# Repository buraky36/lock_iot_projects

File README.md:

# lock_iot_projects
Barfas Projects

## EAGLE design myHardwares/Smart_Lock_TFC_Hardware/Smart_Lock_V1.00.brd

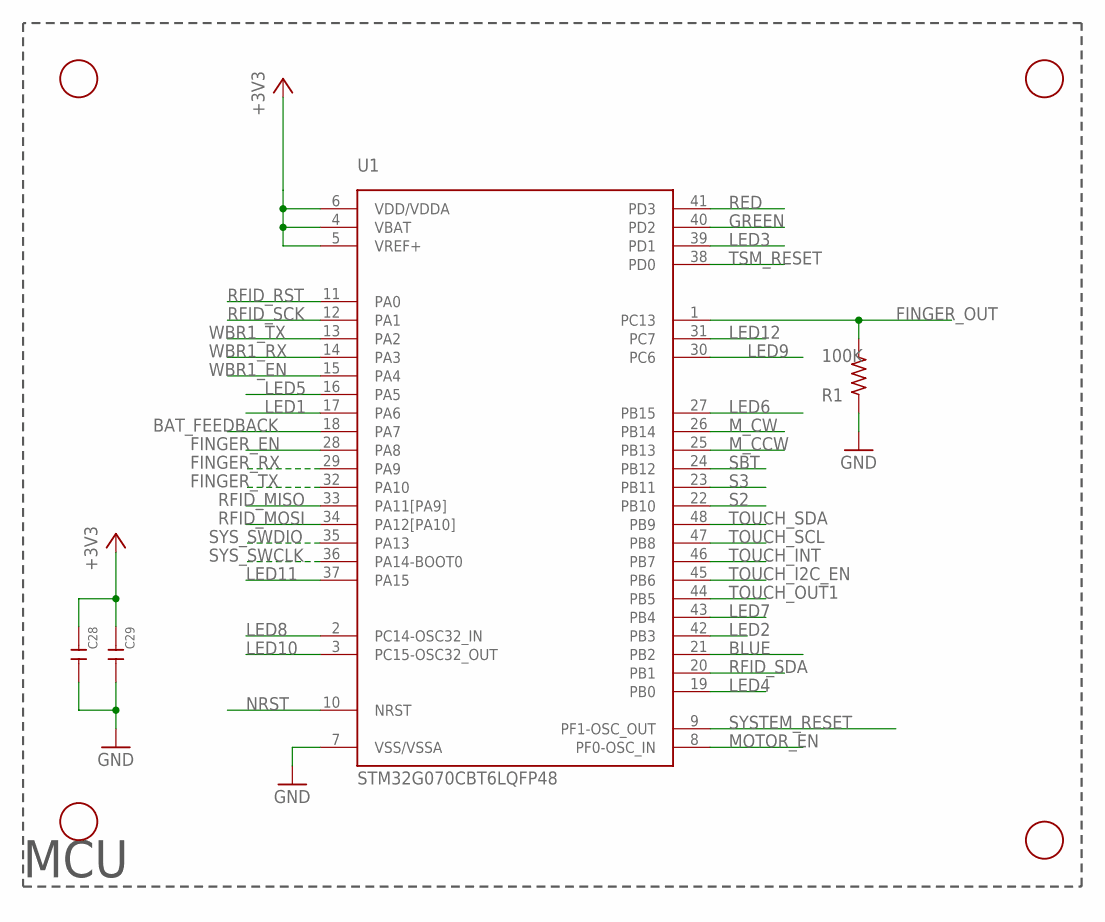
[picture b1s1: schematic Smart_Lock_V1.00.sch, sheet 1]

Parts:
C28, C29: 100nF; C0603
F1, F2, F3, F4: FIDUCIAL; FIDUCIAL_1MM
R1: 100K; R0603
U1: STM32G070CBT6LQFP48; LQFP48

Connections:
+3V3: C28.1, C29.1, U1.4 (VBAT), U1.5 (VREF+), U1.6 (VDD/VDDA); also elsewhere on the board
BAT_FEEDBACK: U1.18 (PA7); also elsewhere on the board
BLUE: U1.21 (PB2); also elsewhere on the board
FINGER_EN: U1.28 (PA8); also elsewhere on the board
FINGER_OUT: R1.1, U1.1 (PC13); also elsewhere on the board
FINGER_RX: U1.29 (PA9); also elsewhere on the board
FINGER_TX: U1.32 (PA10); also elsewhere on the board
GND: C28.2, C29.2, R1.2, U1.7 (VSS/VSSA); also elsewhere on the board
GREEN: U1.40 (PD2); also elsewhere on the board
LED1: U1.17 (PA6); also elsewhere on the board
LED2: U1.42 (PB3); also elsewhere on the board
LED3: U1.39 (PD1); also elsewhere on the board
LED4: U1.19 (PB0); also elsewhere on the board
LED5: U1.16 (PA5); also elsewhere on the board
LED6: U1.27 (PB15); also elsewhere on the board
LED7: U1.43 (PB4); also elsewhere on the board
LED8: U1.2 (PC14-OSC32_IN); also elsewhere on the board
LED9: U1.30 (PC6); also elsewhere on the board
LED10: U1.3 (PC15-OSC32_OUT); also elsewhere on the board
LED11: U1.37 (PA15); also elsewhere on the board
LED12: U1.31 (PC7); also elsewhere on the board
MOTOR_EN: U1.8 (PF0-OSC_IN); also elsewhere on the board
M_CCW: U1.25 (PB13); also elsewhere on the board
M_CW: U1.26 (PB14); also elsewhere on the board
NRST: U1.10 (NRST); also elsewhere on the board
RED: U1.41 (PD3); also elsewhere on the board
RFID_MISO: U1.33 (PA11[PA9]); also elsewhere on the board
RFID_MOSI: U1.34 (PA12[PA10]); also elsewhere on the board
RFID_RST: U1.11 (PA0); also elsewhere on the board
RFID_SCK: U1.12 (PA1); also elsewhere on the board
RFID_SDA: U1.20 (PB1); also elsewhere on the board
S2: U1.22 (PB10); also elsewhere on the board
S3: U1.23 (PB11); also elsewhere on the board
SBT: U1.24 (PB12); also elsewhere on the board
SYSTEM_RESET: U1.9 (PF1-OSC_OUT); also elsewhere on the board
SYS_SWCLK: U1.36 (PA14-BOOT0); also elsewhere on the board
SYS_SWDIO: U1.35 (PA13); also elsewhere on the board
TOUCH_I2C_EN: U1.45 (PB6); also elsewhere on the board
TOUCH_INT: U1.46 (PB7); also elsewhere on the board
TOUCH_OUT1: U1.44 (PB5); also elsewhere on the board
TOUCH_SCL: U1.47 (PB8); also elsewhere on the board
TOUCH_SDA: U1.48 (PB9); also elsewhere on the board
TSM_RESET: U1.38 (PD0); also elsewhere on the board
WBR1_EN: U1.15 (PA4); also elsewhere on the board
WBR1_RX: U1.14 (PA3); also elsewhere on the board
WBR1_TX: U1.13 (PA2); also elsewhere on the board

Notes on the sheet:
MCU

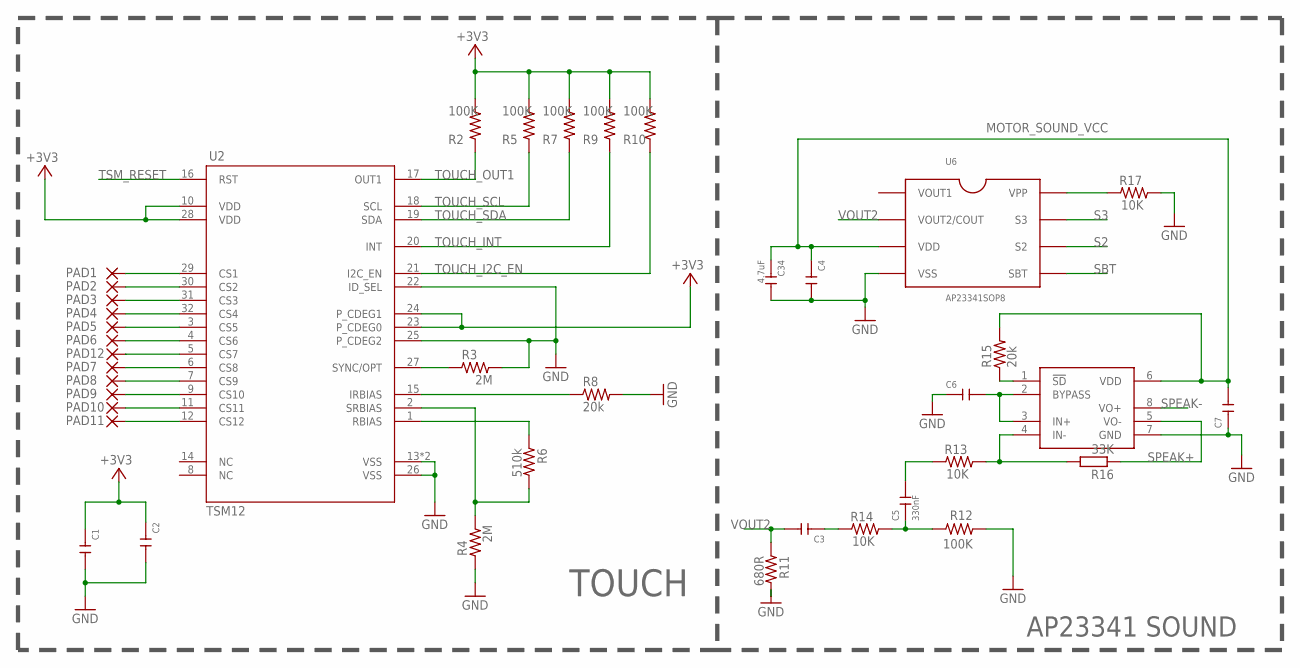
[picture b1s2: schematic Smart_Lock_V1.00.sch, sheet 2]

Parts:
C1, C6, C7: 1uf; C0603
C2, C3, C4: 100nF; C0603
C5: 330nF; C0603
C34: 4.7uF; C0603
PAD1, PAD2, PAD3, PAD4, PAD5, PAD6, PAD7, PAD8, PAD9, PAD10, PAD11, PAD12: WIREPADSMD1,27-254; SMD1,27-2,54
R2, R5, R7, R9, R10, R12: 100K; R0603
R3, R4: 2M; R0603
R6: 510k; R0603
R8, R15: 20k; 0603
R11: 680R; R0603
R13, R14, R17: 10K; R0603
R16: 33K; R0603
U2: TSM12M; QFN_32_UH
U6: AP23341SOP8; SOP8
U7: AP4890; MSOP08

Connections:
+3V3: C1.1, C2.1, R2.1, R5.1, R7.1, R9.1, R10.1, U2.10 (VDD), U2.23 (P_CDEG0), U2.24 (P_CDEG1), U2.28 (VDD); also elsewhere on the board
GND: C1.2, C2.2, C4.2, C6.1, C7.1, C34.2, R3.2, R4.1, R8.2, R11.2, R12.2, R17.2, U2.13 (VSS), U2.22 (ID_SEL), U2.25 (P_CDEG2), U2.26 (VSS), U2.33 (VSS), U6.4 (VSS), U7.7 (GND); also elsewhere on the board
MOTOR_SOUND_VCC: C4.1, C7.2, C34.1, R15.2, U6.3 (VDD), U7.6 (VDD); also elsewhere on the board
unnamed: R17.1, U6.8 (VPP)
unnamed: R15.1, U7.1 (!SD)
unnamed: PAD3.1, U2.31 (CS3)
unnamed: C6.2, U7.2 (BYPASS), U7.3 (IN+)
unnamed: C5.2, R13.1
unnamed: R3.1, U2.27 (SYNC/OPT)
unnamed: R13.2, R16.2, U7.4 (IN-)
unnamed: C3.1, R14.1
unnamed: PAD4.1, U2.32 (CS4)
unnamed: PAD5.1, U2.3 (CS5)
unnamed: PAD6.1, U2.4 (CS6)
unnamed: PAD2.1, U2.30 (CS2)
unnamed: PAD1.1, U2.29 (CS1)
unnamed: PAD7.1, U2.6 (CS8)
unnamed: PAD9.1, U2.9 (CS10)
unnamed: PAD10.1, U2.11 (CS11)
unnamed: R6.1, U2.1 (RBIAS)
unnamed: PAD11.1, U2.12 (CS12)
unnamed: R4.2, R6.2, U2.2 (SRBIAS)
unnamed: PAD12.1, U2.5 (CS7)
unnamed: R8.1, U2.15 (IRBIAS)
unnamed: PAD8.1, U2.7 (CS9)
unnamed: C5.1, R12.1, R14.2
S2: U6.6 (S2); also elsewhere on the board
S3: U6.7 (S3); also elsewhere on the board
SBT: U6.5 (SBT); also elsewhere on the board
SPEAK+: R16.1, U7.5 (VO-); also elsewhere on the board
SPEAK-: U7.8 (VO+); also elsewhere on the board
TOUCH_I2C_EN: R10.2, U2.21 (I2C_EN); also elsewhere on the board
TOUCH_INT: R9.2, U2.20 (INT); also elsewhere on the board
TOUCH_OUT1: R2.2, U2.17 (OUT1); also elsewhere on the board
TOUCH_SCL: R5.2, U2.18 (SCL); also elsewhere on the board
TOUCH_SDA: R7.2, U2.19 (SDA); also elsewhere on the board
TSM_RESET: U2.16 (RST); also elsewhere on the board
VOUT2: C3.2, R11.1, U6.2 (VOUT2/COUT)

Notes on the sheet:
TOUCH
AP23341 SOUND

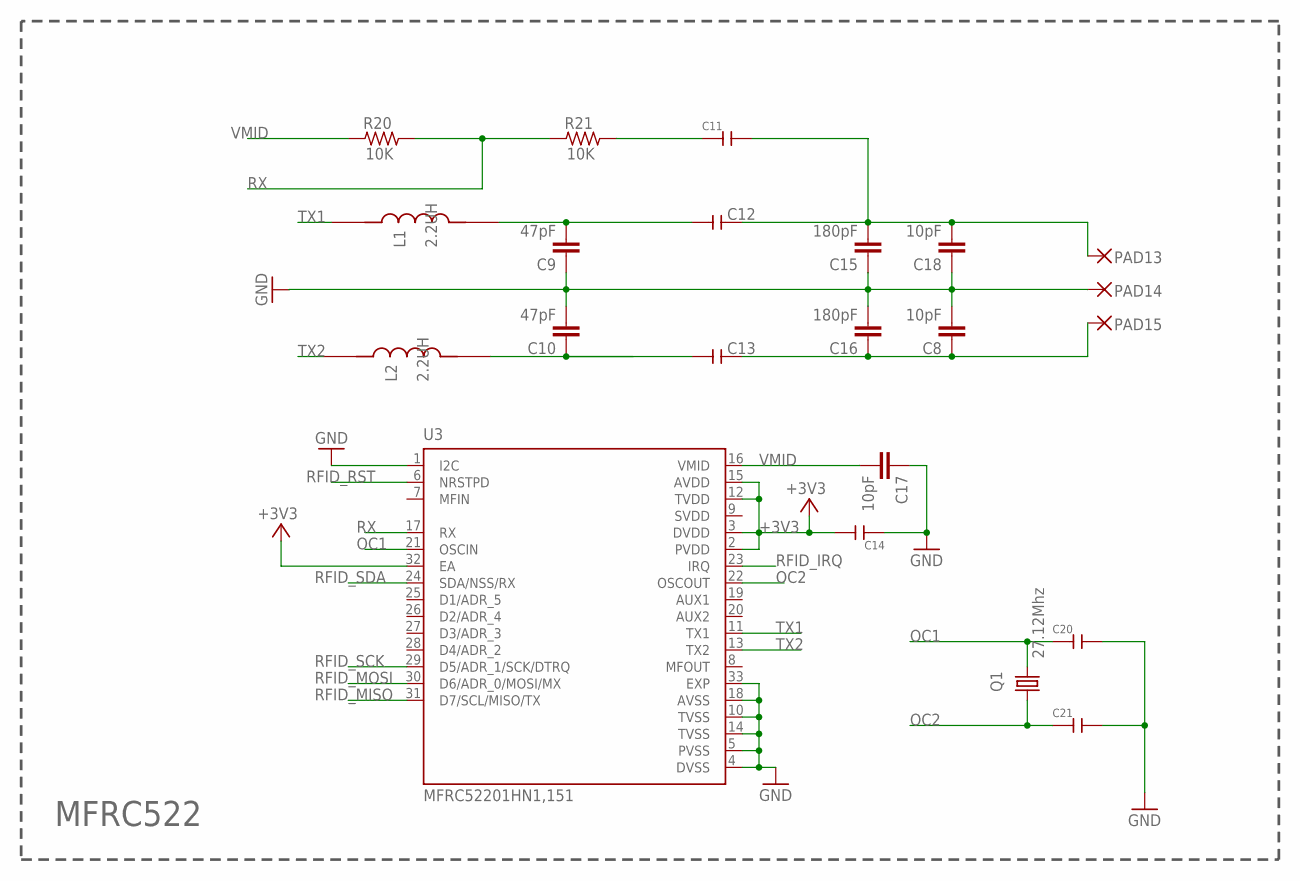
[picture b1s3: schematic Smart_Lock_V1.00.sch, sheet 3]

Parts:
C8, C17, C18: 10pF; C0603
C9, C10: 47pF; C0603
C11, C14: 100nF; C0603
C12, C13, C20, C21: 15pf; C0603
C15, C16: 180pF; C0603
L1, L2: 2.2UH; INDC2012X105N
PAD13, PAD14, PAD15: WIREPADSMD5-1,8; 5-1,8
Q1: 27.12Mhz; 2.5X2.0_KX-6
R20, R21: 10K; R0603
U3: MFRC52201HN1,151; QFN50P500X500X100-33N

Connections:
+3V3: C14.2, U3.2 (PVDD), U3.3 (DVDD), U3.12 (TVDD), U3.15 (AVDD), U3.32 (EA); also elsewhere on the board
ANT: C11.2, C12.2, C15.2, C18.2, PAD13.1
ANT2: C8.1, C13.2, C16.1, PAD15.1
GND: C8.2, C9.1, C10.2, C14.1, C15.1, C16.2, C17.1, C18.1, C20.2, C21.2, PAD14.1, U3.1 (I2C), U3.4 (DVSS), U3.5 (PVSS), U3.10 (TVSS), U3.14 (TVSS), U3.18 (AVSS), U3.33 (EXP); also elsewhere on the board
unnamed: C11.1, R21.2
unnamed: C9.2, C12.1, L1.2
unnamed: C10.1, C13.1, L2.2
OC1: C20.1, Q1.3 (2), U3.21 (OSCIN)
OC2: C21.1, Q1.1, U3.22 (OSCOUT)
RFID_IRQ: U3.23 (IRQ)
RFID_MISO: U3.31 (D7/SCL/MISO/TX); also elsewhere on the board
RFID_MOSI: U3.30 (D6/ADR_0/MOSI/MX); also elsewhere on the board
RFID_RST: U3.6 (NRSTPD); also elsewhere on the board
RFID_SCK: U3.29 (D5/ADR_1/SCK/DTRQ); also elsewhere on the board
RFID_SDA: U3.24 (SDA/NSS/RX); also elsewhere on the board
RX: R20.2, R21.1, U3.17 (RX)
SVDD: U3.9 (SVDD)
TX1: L1.1, U3.11 (TX1)
TX2: L2.1, U3.13 (TX2)
VMID: C17.2, R20.1, U3.16 (VMID)

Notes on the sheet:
MFRC522

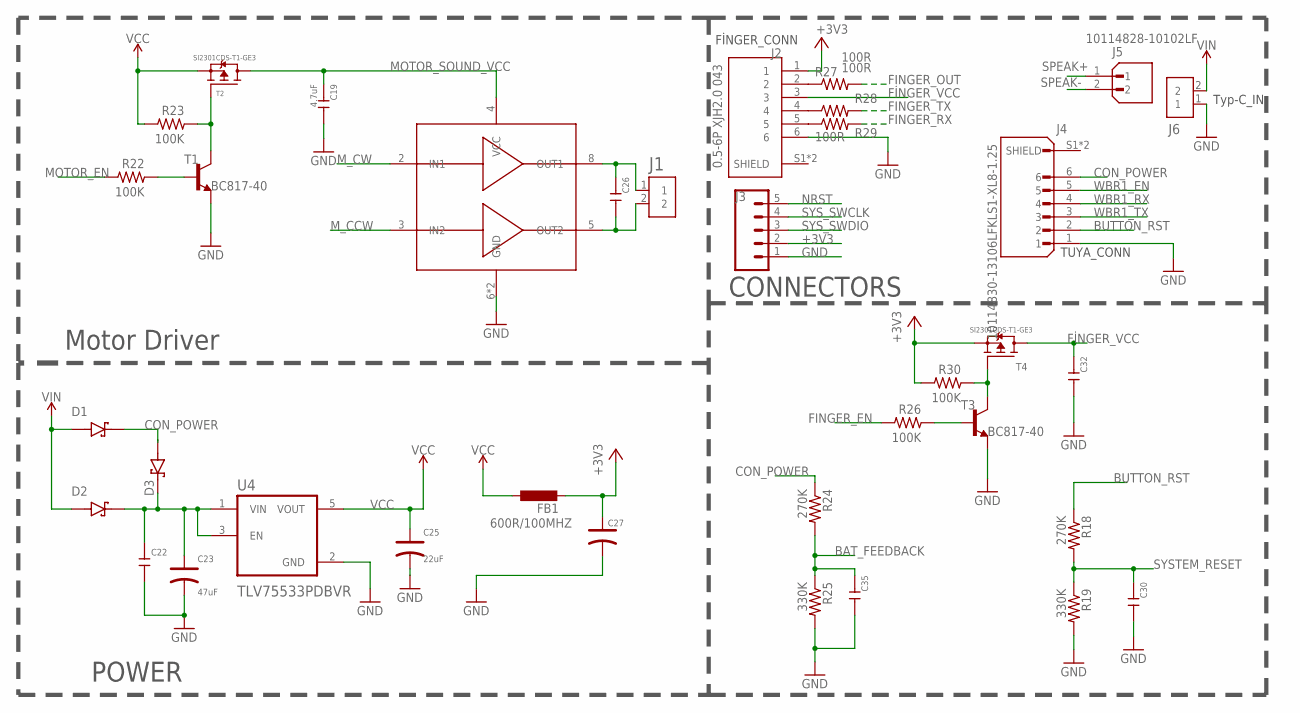
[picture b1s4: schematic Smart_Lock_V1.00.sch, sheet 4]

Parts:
C19: 4.7uF; C0603
C22, C26, C30, C32, C35: 100nF; C0603
C23: 47uF; AVX-B
C25: 22uF; CT1206
C27: 10uf; AVX-B
D1, D2, D3: 1N5819HW-7-F; SOD3715X145N
FB1: 600R/100MHZ; L2012C
J1, J6: B2B-PH-SM4-TB(LF)(SN)
J2: 0.5-6P XJH2.0 043; WE_68710614522
J3: CONN_05; 1X05
J4: 10114830-13106LFKLS1-XL8-1.25; 1X6PIN_1.25MM
J5: 10114828-10102LF; AMPHENOL_10114828-10102LF
R18, R24: 270K; 0603
R19, R25: 330K; 0603
R22, R23, R26, R30: 100K; R0603
R27, R28, R29: 100R; R0402
T1, T3: BC817-40; SOT23-BEC
T2, T4: SI2301CDS-T1-GE3; SOT-23
U4: TLV75533PDBVR; SOT95P285X140-5N
U5: TC118S8; SO08

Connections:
+3V3: C27.+, FB1.2, J2.1, J3.2, R30.1, T4.2 (S); also elsewhere on the board
BAT_FEEDBACK: C35.1, R24.2, R25.1; also elsewhere on the board
BUTTON_RST: J4.2, R18.1
CON_POWER: D1.C (K), D3.A, J4.6, R24.1
FINGER_EN: R26.1; also elsewhere on the board
FINGER_OUT: R27.2; also elsewhere on the board
FINGER_RX: R29.2; also elsewhere on the board
FINGER_TX: R28.2; also elsewhere on the board
FİNGER_VCC: C32.1, J2.3, T4.3 (D)
GND: C19.2, C22.2, C23.-, C25.-, C27.-, C30.2, C32.2, C35.2, J2.6, J3.1, J4.1, J6.1, R19.2, R25.2, T1.E, T3.E, U4.2 (GND), U5.6 (GND), U5.7 (GND); also elsewhere on the board
MOTOR_EN: R22.1; also elsewhere on the board
MOTOR_SOUND_VCC: C19.1, T2.3 (D), U5.4 (VCC); also elsewhere on the board
M_CCW: U5.3 (IN2); also elsewhere on the board
M_CW: U5.2 (IN1); also elsewhere on the board
unnamed: C22.1, C23.+, D2.C (K), D3.C (K), U4.1 (VIN), U4.3 (EN)
unnamed: C26.1, J1.1, U5.8 (OUT1)
unnamed: R26.2, T3.B
unnamed: C26.2, J1.2, U5.5 (OUT2)
unnamed: R30.2, T3.C, T4.1 (G)
unnamed: R22.2, T1.B
unnamed: R23.2, T1.C, T2.1 (G)
unnamed: J2.2, R27.1
unnamed: J2.4, R28.1
unnamed: J2.5, R29.1
NRST: J3.5; also elsewhere on the board
SPEAK+: J5.1; also elsewhere on the board
SPEAK-: J5.2; also elsewhere on the board
SYSTEM_RESET: C30.1, R18.2, R19.1; also elsewhere on the board
SYS_SWCLK: J3.4; also elsewhere on the board
SYS_SWDIO: J3.3; also elsewhere on the board
VCC: C25.+, FB1.1, R23.1, T2.2 (S), U4.5 (VOUT)
VIN: D1.A, D2.A, J6.2
WBR1_EN: J4.5; also elsewhere on the board
WBR1_RX: J4.4; also elsewhere on the board
WBR1_TX: J4.3; also elsewhere on the board

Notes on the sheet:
POWER
CONNECTORS
Motor Driver
Typ-C_IN
TUYA_CONN
FİNGER_CONN

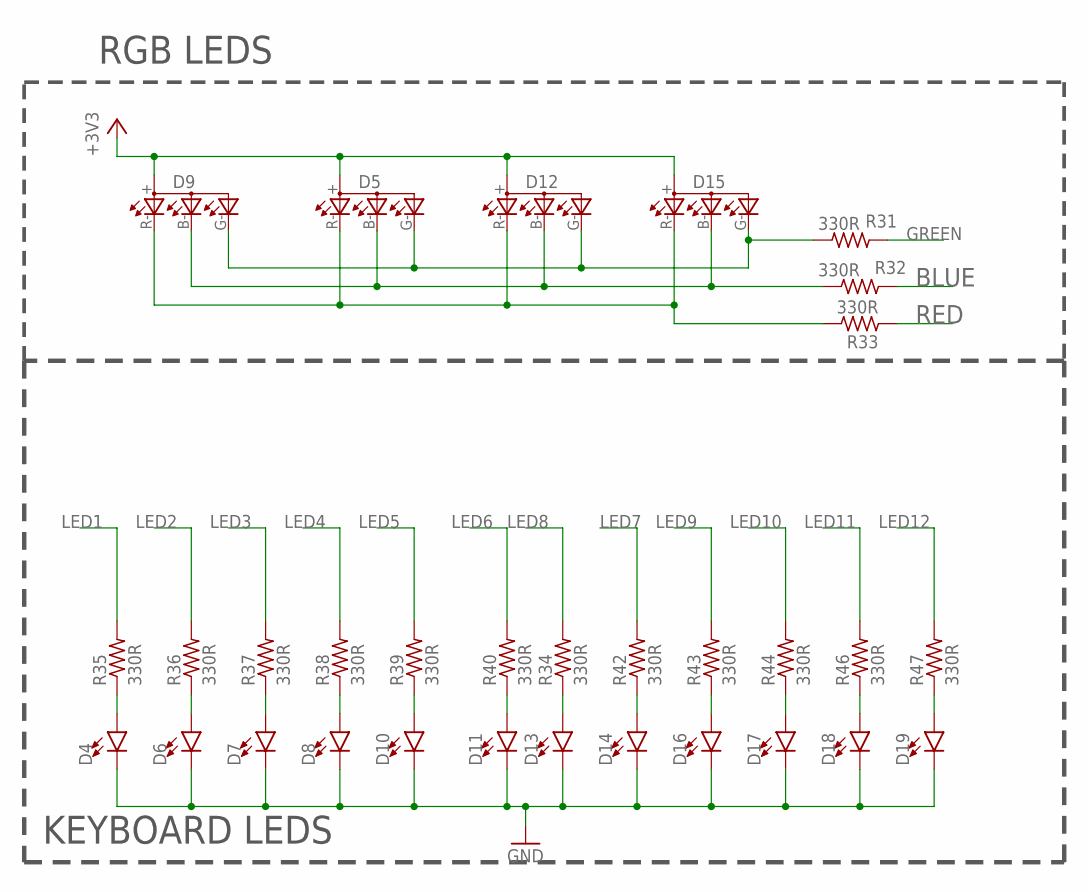
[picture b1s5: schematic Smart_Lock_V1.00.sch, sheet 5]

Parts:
D4, D6, D7, D8, D10, D11, D13, D14, D16, D17, D18, D19: HL-PST-1608H233W-HF4; LED-0603
D5, D9, D12, D15: FM-3510RGBA-SG; SMD-4P,1X3MM
R31, R32, R33: 330R; R0603
R34, R35, R36, R37, R38, R39, R40, R42, R43, R44, R46, R47: 330R; R0402

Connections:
+3V3: D5.+ (A), D9.+ (A), D12.+ (A), D15.+ (A); also elsewhere on the board
BLUE: R32.2; also elsewhere on the board
GND: D4.C, D6.C, D7.C, D8.C, D10.C, D11.C, D13.C, D14.C, D16.C, D17.C, D18.C, D19.C; also elsewhere on the board
GREEN: R31.2; also elsewhere on the board
LED1: R35.2; also elsewhere on the board
LED2: R36.2; also elsewhere on the board
LED3: R37.2; also elsewhere on the board
LED4: R38.2; also elsewhere on the board
LED5: R39.2; also elsewhere on the board
LED6: R40.2; also elsewhere on the board
LED7: R42.2; also elsewhere on the board
LED8: R34.2; also elsewhere on the board
LED9: R43.2; also elsewhere on the board
LED10: R44.2; also elsewhere on the board
LED11: R46.2; also elsewhere on the board
LED12: R47.2; also elsewhere on the board
unnamed: D13.A, R34.1
unnamed: D5.G- (CGREEN), D9.G- (CGREEN), D12.G- (CGREEN), D15.G- (CGREEN), R31.1
unnamed: D5.B- (CBLUE), D9.B- (CBLUE), D12.B- (CBLUE), D15.B- (CBLUE), R32.1
unnamed: D4.A, R35.1
unnamed: D6.A, R36.1
unnamed: D5.R- (CRED), D9.R- (CRED), D12.R- (CRED), D15.R- (CRED), R33.1
unnamed: D7.A, R37.1
unnamed: D8.A, R38.1
unnamed: D10.A, R39.1
unnamed: D11.A, R40.1
unnamed: D14.A, R42.1
unnamed: D16.A, R43.1
unnamed: D17.A, R44.1
unnamed: D18.A, R46.1
unnamed: D19.A, R47.1
RED: R33.2; also elsewhere on the board

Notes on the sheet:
KEYBOARD LEDS
RGB LEDS

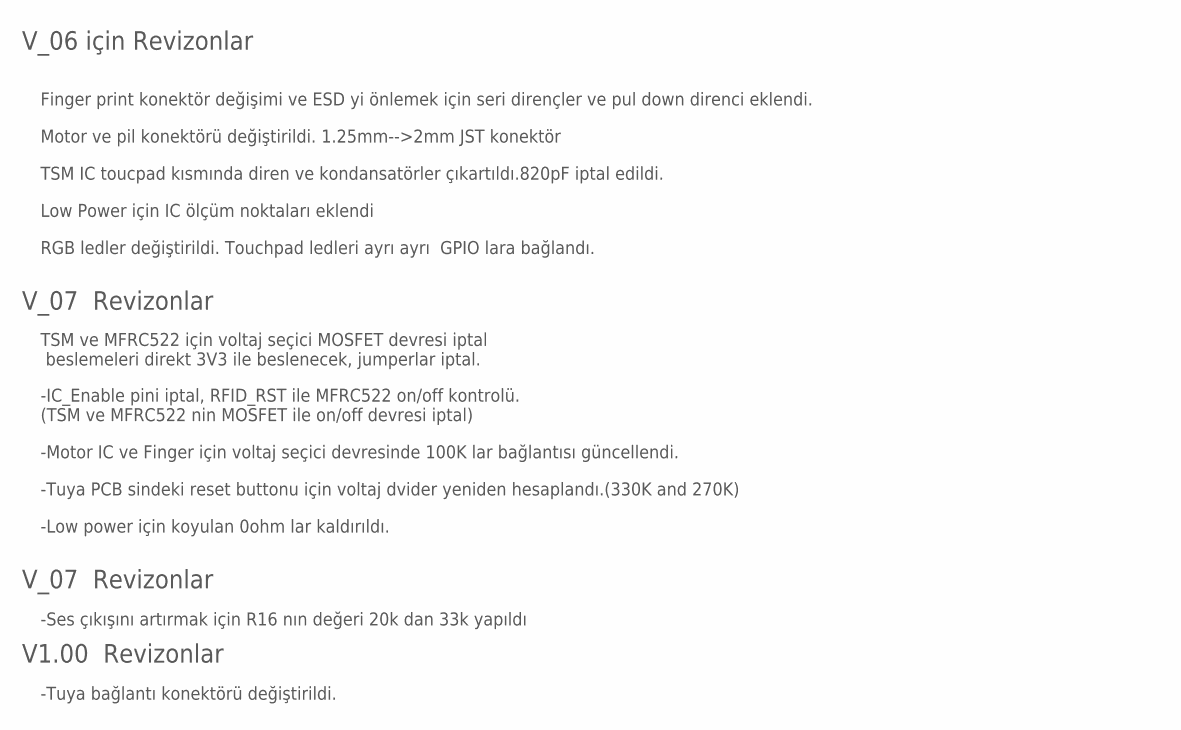
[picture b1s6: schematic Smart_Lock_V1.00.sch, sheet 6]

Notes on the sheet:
Finger print konektör değişimi ve ESD yi önlemek için seri dirençler ve pul down direnci eklendi.
Motor ve pil konektörü değiştirildi. 1.25mm-->2mm JST konektör
TSM IC toucpad kısmında diren ve kondansatörler çıkartıldı.820pF iptal edildi.
Low Power için IC ölçüm noktaları eklendi
RGB ledler değiştirildi. Touchpad ledleri ayrı ayrı GPIO lara bağlandı.
V_06 için Revizonlar
V_07 Revizonlar
TSM ve MFRC522 için voltaj seçici MOSFET devresi iptal beslemeleri direkt 3V3 ile beslenecek, jumperlar iptal.
-IC_Enable pini iptal, RFID_RST ile MFRC522 on/off kontrolü. (TSM ve MFRC522 nin MOSFET ile on/off devresi iptal)
-Motor IC ve Finger için voltaj seçici devresinde 100K lar bağlantısı güncellendi.
-Tuya PCB sindeki reset buttonu için voltaj dvider yeniden hesaplandı.(330K and 270K)
-Low power için koyulan 0ohm lar kaldırıldı.
-Ses çıkışını artırmak için R16 nın değeri 20k dan 33k yapıldı
V1.00 Revizonlar
-Tuya bağlantı konektörü değiştirildi.

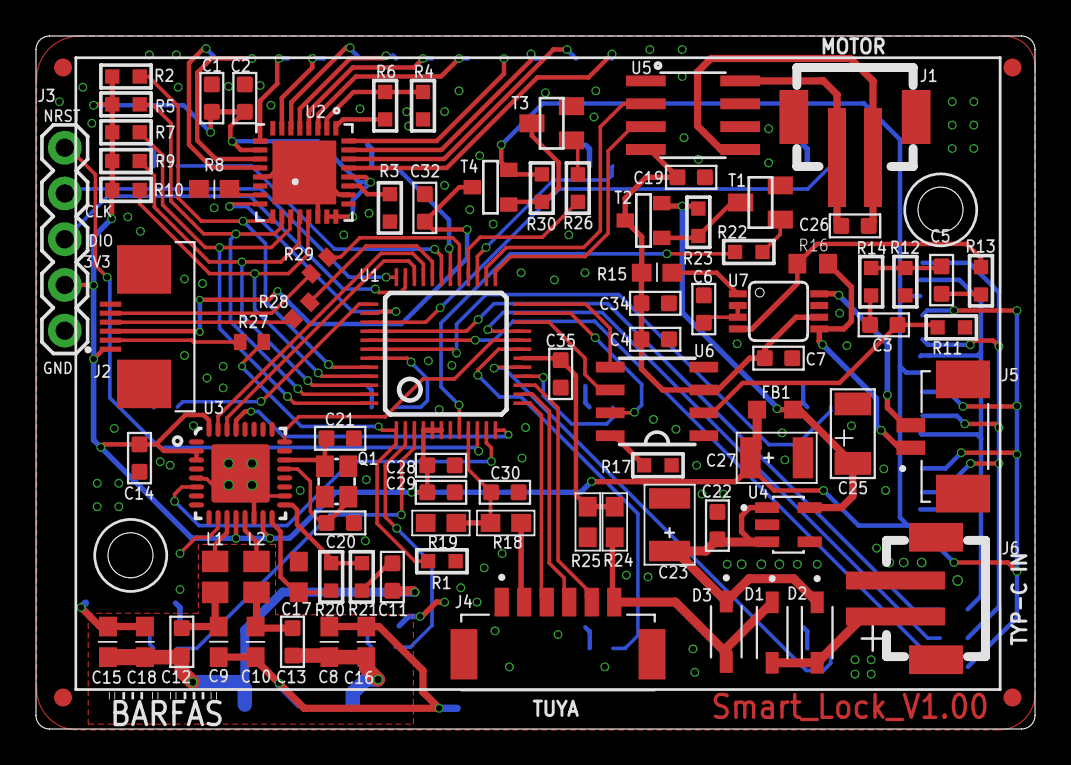
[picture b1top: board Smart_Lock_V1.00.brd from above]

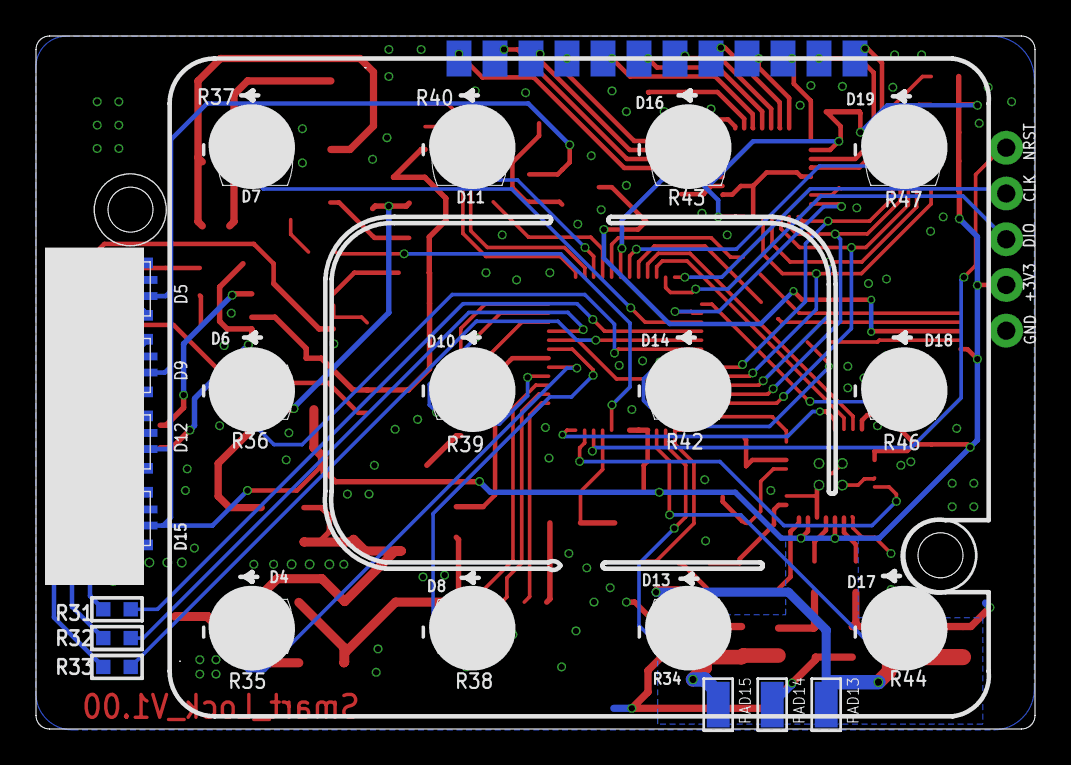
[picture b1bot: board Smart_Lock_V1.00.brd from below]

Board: 2 copper layers, 55.5 x 38.5 mm, 136 parts (46 on the bottom side), 114 nets.

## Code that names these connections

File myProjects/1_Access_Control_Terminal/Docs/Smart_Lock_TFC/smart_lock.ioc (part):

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Mcu.Name=STM32G070CBTx
Mcu.Package=LQFP48
Mcu.UserName=STM32G070CBTx
PA0.GPIOParameters=PinState,GPIO_PuPd,GPIO_Label
PA0.GPIO_Label=IC_ENABLE
PA0.GPIO_PuPd=GPIO_NOPULL
PA0.PinState=GPIO_PIN_RESET
PA0.Signal=GPIO_Output
PA1.GPIOParameters=GPIO_Label
PA1.GPIO_Label=SPI_RFID_SCK
PA1.Mode=Full_Duplex_Master
PA1.Signal=SPI1_SCK
PA10.GPIOParameters=GPIO_Label
PA10.GPIO_Label=USART_FP_Rx
PA10.Mode=Asynchronous
PA10.Signal=USART1_RX
PA11\ [PA9].GPIOParameters=GPIO_Label
PA11\ [PA9].GPIO_Label=SPI_RFID_MISO
PA11\ [PA9].Mode=Full_Duplex_Master
PA11\ [PA9].Signal=SPI1_MISO
PA12\ [PA10].GPIOParameters=GPIO_Label
PA12\ [PA10].GPIO_Label=SPI_RFID_MOSI
PA12\ [PA10].Mode=Full_Duplex_Master
PA12\ [PA10].Signal=SPI1_MOSI
PA13.Mode=Serial_Wire
PA13.Signal=SYS_SWDIO
PA14-BOOT0.Mode=Serial_Wire
PA14-BOOT0.Signal=SYS_SWCLK
PA15.GPIOParameters=GPIO_Label
PA15.GPIO_Label=LED11
PA15.Signal=GPIO_Output
PA2.GPIOParameters=GPIO_Label
PA2.GPIO_Label=WBR1_TX
PA2.Mode=Asynchronous
PA2.Signal=USART2_TX
PA3.GPIOParameters=GPIO_Label
PA3.GPIO_Label=WBR1_RX
PA3.Mode=Asynchronous
PA3.Signal=USART2_RX
PA4.GPIOParameters=GPIO_PuPd,GPIO_Label
PA4.GPIO_Label=WBR1_EN
PA4.GPIO_PuPd=GPIO_NOPULL
PA4.Signal=GPIO_Output
PA5.GPIOParameters=GPIO_Label
PA5.GPIO_Label=LED5
PA5.Signal=GPIO_Output
PA6.GPIOParameters=GPIO_Label
PA6.GPIO_Label=LED1
PA6.Signal=GPIO_Output
PA7.GPIOParameters=GPIO_Label
PA7.GPIO_Label=BAT_VOLTAGE
PA7.Mode=IN7
PA7.Signal=ADC1_IN7
PA8.GPIOParameters=GPIO_Label
PA8.GPIO_Label=FP_EN_VCC
PA8.Signal=GPIO_Output
PA9.GPIOParameters=GPIO_Label
PA9.GPIO_Label=USART_FP_Tx
PA9.Mode=Asynchronous
PA9.Signal=USART1_TX
PB0.GPIOParameters=GPIO_Label
PB0.GPIO_Label=LED4
PB0.Signal=GPIO_Output
PB1.GPIOParameters=GPIO_Label
PB1.GPIO_Label=Out_RFID_NSS
PB1.Signal=GPIO_Output
PB10.Mode=TX_Only_Simplex_Unidirect_Master
PB10.Signal=SPI2_SCK
PB11.Mode=TX_Only_Simplex_Unidirect_Master
PB11.Signal=SPI2_MOSI
PB12.GPIOParameters=GPIO_Label
PB12.GPIO_Label=Out_AP23_SBT
PB12.Signal=GPIO_Output
PB13.GPIOParameters=GPIO_Label
PB13.GPIO_Label=Motor_CCW
PB13.Signal=GPIO_Output
PB14.GPIOParameters=GPIO_Label
PB14.GPIO_Label=Motor_CW
PB14.Signal=GPIO_Output
PB15.GPIOParameters=GPIO_Label
PB15.GPIO_Label=LED6
PB15.Signal=GPIO_Output
PB2.GPIOParameters=GPIO_Label
PB2.GPIO_Label=RGB_GREEN
PB2.Signal=GPIO_Output
PB3.GPIOParameters=GPIO_Label
PB3.GPIO_Label=LED2
PB3.Signal=GPIO_Output
PB4.GPIOParameters=GPIO_Label
PB4.GPIO_Label=LED8
PB4.Signal=GPIO_Output
PB5.Signal=GPIO_Output
PB6.Signal=GPIO_Output
PB7.GPIOParameters=GPIO_Label,GPIO_ModeDefaultEXTI
PB7.GPIO_Label=TOUCH_INT
PB7.GPIO_ModeDefaultEXTI=GPIO_MODE_IT_FALLING
PB7.Signal=GPXTI7
PB8.GPIOParameters=GPIO_Label
PB8.GPIO_Label=I2C_Tsm_SCL
PB8.Mode=I2C
PB8.Signal=I2C1_SCL
PB9.GPIOParameters=GPIO_Label
PB9.GPIO_Label=I2C1_Tsm_SDA
PB9.Mode=I2C
PB9.Signal=I2C1_SDA
PC13.GPIOParameters=GPIO_Label
PC13.GPIO_Label=EXTI_FP_Touch
PC13.Signal=GPXTI13
PC14-OSC32_IN\ (PC14).GPIOParameters=GPIO_Label
PC14-OSC32_IN\ (PC14).GPIO_Label=LED7
PC14-OSC32_IN\ (PC14).Signal=GPIO_Output
PC15-OSC32_OUT\ (PC15).GPIOParameters=GPIO_Label
PC15-OSC32_OUT\ (PC15).GPIO_Label=LED10
PC15-OSC32_OUT\ (PC15).Signal=GPIO_Output
PC6.GPIOParameters=GPIO_Label
PC6.GPIO_Label=LED9
PC6.Signal=GPIO_Output
PC7.GPIOParameters=GPIO_Label
PC7.GPIO_Label=LED12
PC7.Signal=GPIO_Output
PD0.GPIOParameters=GPIO_Speed,GPIO_PuPd,GPIO_Label
PD0.GPIO_Label=TSM_RESET
PD0.GPIO_PuPd=GPIO_PULLDOWN
PD0.GPIO_Speed=GPIO_SPEED_FREQ_HIGH
PD0.Signal=GPIO_Output
PD1.GPIOParameters=GPIO_Label
PD1.GPIO_Label=LED3
PD1.Signal=GPIO_Output
PD2.GPIOParameters=GPIO_Label
PD2.GPIO_Label=RGB_BLUE
PD2.Signal=GPIO_Output
PD3.GPIOParameters=GPIO_Label
PD3.GPIO_Label=RGB_RED
PD3.Signal=GPIO_Output
PF0-OSC_IN\ (PF0).GPIOParameters=GPIO_PuPd,GPIO_Label
PF0-OSC_IN\ (PF0).GPIO_Label=MOTOR_ENABLE
PF0-OSC_IN\ (PF0).GPIO_PuPd=GPIO_NOPULL
PF0-OSC_IN\ (PF0).Signal=GPIO_Output
PF1-OSC_OUT\ (PF1).GPIOParameters=GPIO_Label,GPIO_ModeDefaultEXTI
PF1-OSC_OUT\ (PF1).GPIO_Label=SYSTEM_RESET_INT
PF1-OSC_OUT\ (PF1).GPIO_ModeDefaultEXTI=GPIO_MODE_IT_RISING
PF1-OSC_OUT\ (PF1).Signal=GPXTI1
RCC.HSE_VALUE=8000000
RCC.SYSCLKFreq_VALUE=64000000
RCC.SYSCLKSource=RCC_SYSCLKSOURCE_PLLCLK
board=custom

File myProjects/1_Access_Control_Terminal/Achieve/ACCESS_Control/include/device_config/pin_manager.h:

#ifndef PIN_MANAGER_H
#define PIN_MANAGER_H

/*
 * Hardware Pin Definitions for Smart Access Control Terminal
 * Centralized mapping to allow easy adaptation to different MCUs.
 */

// MFRC522 (RFID) SPI Pins
#define PIN_RFID_MOSI 23
#define PIN_RFID_MISO 19
#define PIN_RFID_CLK 18
#define PIN_RFID_CS 5
#define PIN_RFID_IRQ 22
#define PIN_RFID_RST 21

// TSM12 (Touch keypad) I2C Pins
#define PIN_TSM12_SDA 25
#define PIN_TSM12_SCL 26
#define PIN_TSM12_INT 27
#define PIN_TSM12_OUT 14
#define PIN_TSM12_RST 12

// XR1300 (QR Reader) UART Pins
#define PIN_QR_TX 17
#define PIN_QR_RX 16

// 74HC595 Shift Register Pins
#define PIN_SR_CLK 32
#define PIN_SR_DATA 33
#define PIN_SR_LATCH1 25
#define PIN_SR_LATCH2 26

// Buzzer PWM Pin
#define PIN_BUZZER_PWM 13

// Wiegand (Input/Output) Pins
#define PIN_WIEGAND_D0 4
#define PIN_WIEGAND_D1 15

// RS485 Pins
#define PIN_RS485_RX 34
#define PIN_RS485_TX 35
#define PIN_RS485_DE_RE 36 // Data Enable / Receive Enable

// Digital INPUT
#define PIN_DIGITAL_IN 39 // Example input pin
#define PIN_DOOR_SENSOR 39
#define PIN_EXIT_BUTTON 36

// Hardware Interfaces Definitions
#define I2C_PORT_TSM12 I2C_NUM_0
#define UART_PORT_QR UART_NUM_1

#endif // PIN_MANAGER_H

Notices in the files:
parts and their libraries:
cap_master-smd: Copyright (C) 2007, Bob Starr
crystal-geyer_V1_0: Copyright: Geyer-Electronic
SparkFun-LED: Licensing: Creative Commons ShareAlike 4.0 International - https://creativecommons.org/licenses/by-sa/4.0
